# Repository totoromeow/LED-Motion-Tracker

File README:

Computer Science House - LED Motion Tracker 

Anqi Chen (c) 2012

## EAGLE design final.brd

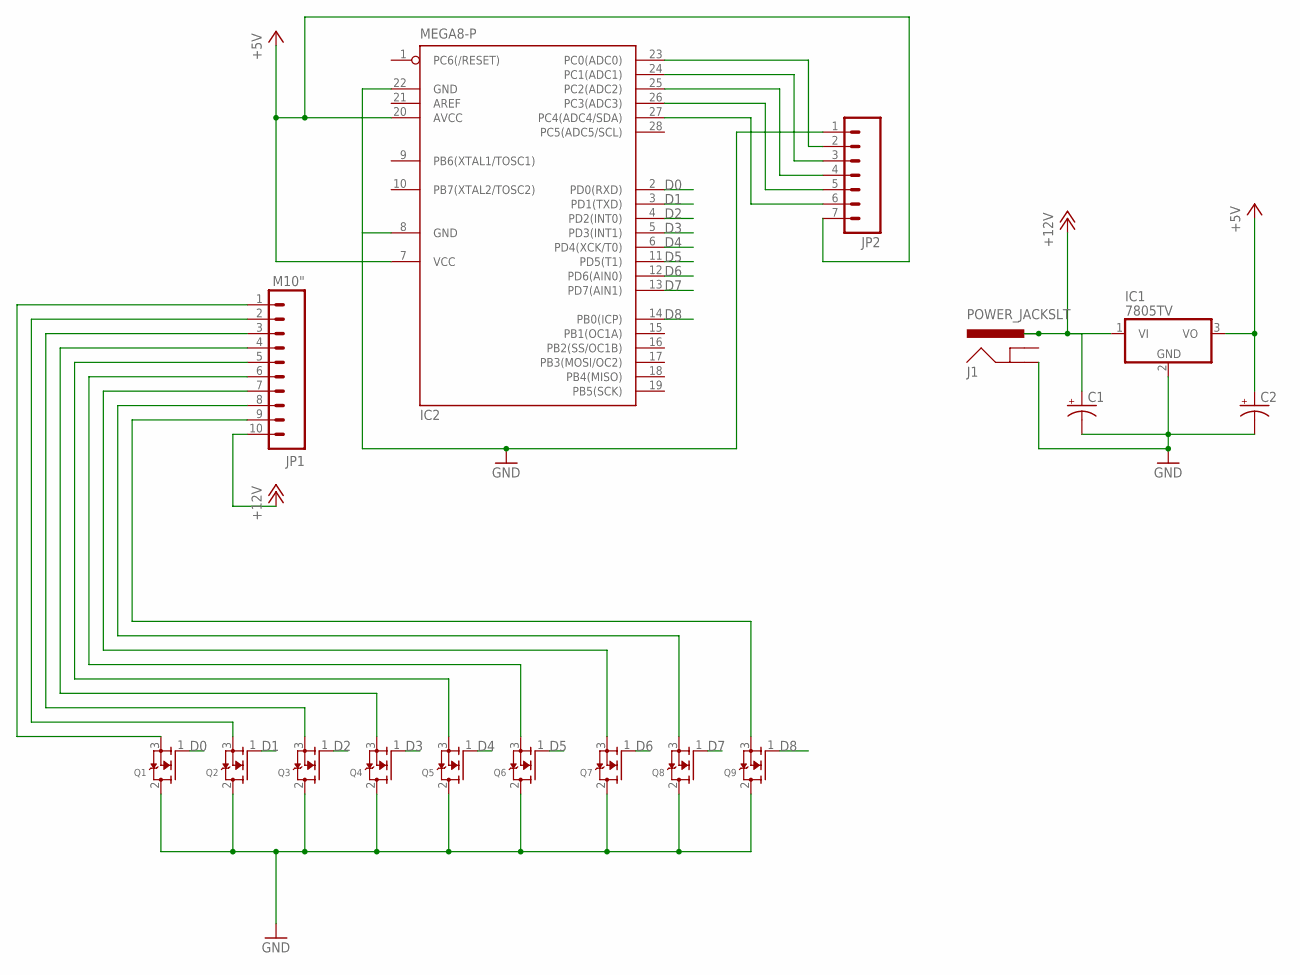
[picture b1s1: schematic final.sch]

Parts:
C1, C2: CAP_POLPTH1; CPOL-RADIAL-100UF-25V
IC1: 7805TV; TO220V
IC2: MEGA8-P; DIL28-3
J1: POWER_JACKSLT; POWER_JACK_SLOT
JP1: M10"; 1X10
JP2: M07; 1X07
Q1, Q2, Q3, Q4, Q5, Q6, Q7, Q8, Q9: MOSFET-NGDS_TO220V; TO220V

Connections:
+5V: C2.1 (+), IC1.3 (VO), IC2.7 (VCC), IC2.20 (AVCC), JP2.7
+12V: C1.1 (+), IC1.1 (VI), J1.PWR, JP1.10
D0: IC2.2 (PD0(RXD)), Q1.1 (G)
D1: IC2.3 (PD1(TXD)), Q2.1 (G)
D2: IC2.4 (PD2(INT0)), Q3.1 (G)
D3: IC2.5 (PD3(INT1)), Q4.1 (G)
D4: IC2.6 (PD4(XCK/T0)), Q5.1 (G)
D5: IC2.11 (PD5(T1)), Q6.1 (G)
D6: IC2.12 (PD6(AIN0)), Q7.1 (G)
D7: IC2.13 (PD7(AIN1)), Q8.1 (G)
D8: IC2.14 (PB0(ICP)), Q9.1 (G)
GND: C1.2 (-), C2.2 (-), IC1.2 (GND), IC2.8 (GND), IC2.22 (GND), J1.GND@2 (GND), JP2.1, Q1.2 (D), Q2.2 (D), Q3.2 (D), Q4.2 (D), Q5.2 (D), Q6.2 (D), Q7.2 (D), Q8.2 (D), Q9.2 (D)
unnamed: JP1.1, Q1.3 (S)
unnamed: JP1.2, Q2.3 (S)
unnamed: JP1.3, Q3.3 (S)
unnamed: IC2.27 (PC4(ADC4/SDA)), JP2.6
unnamed: IC2.23 (PC0(ADC0)), JP2.2
unnamed: IC2.24 (PC1(ADC1)), JP2.3
unnamed: IC2.25 (PC2(ADC2)), JP2.4
unnamed: IC2.26 (PC3(ADC3)), JP2.5
unnamed: JP1.4, Q4.3 (S)
unnamed: JP1.5, Q5.3 (S)
unnamed: JP1.6, Q6.3 (S)
unnamed: JP1.7, Q7.3 (S)
unnamed: JP1.8, Q8.3 (S)
unnamed: JP1.9, Q9.3 (S)

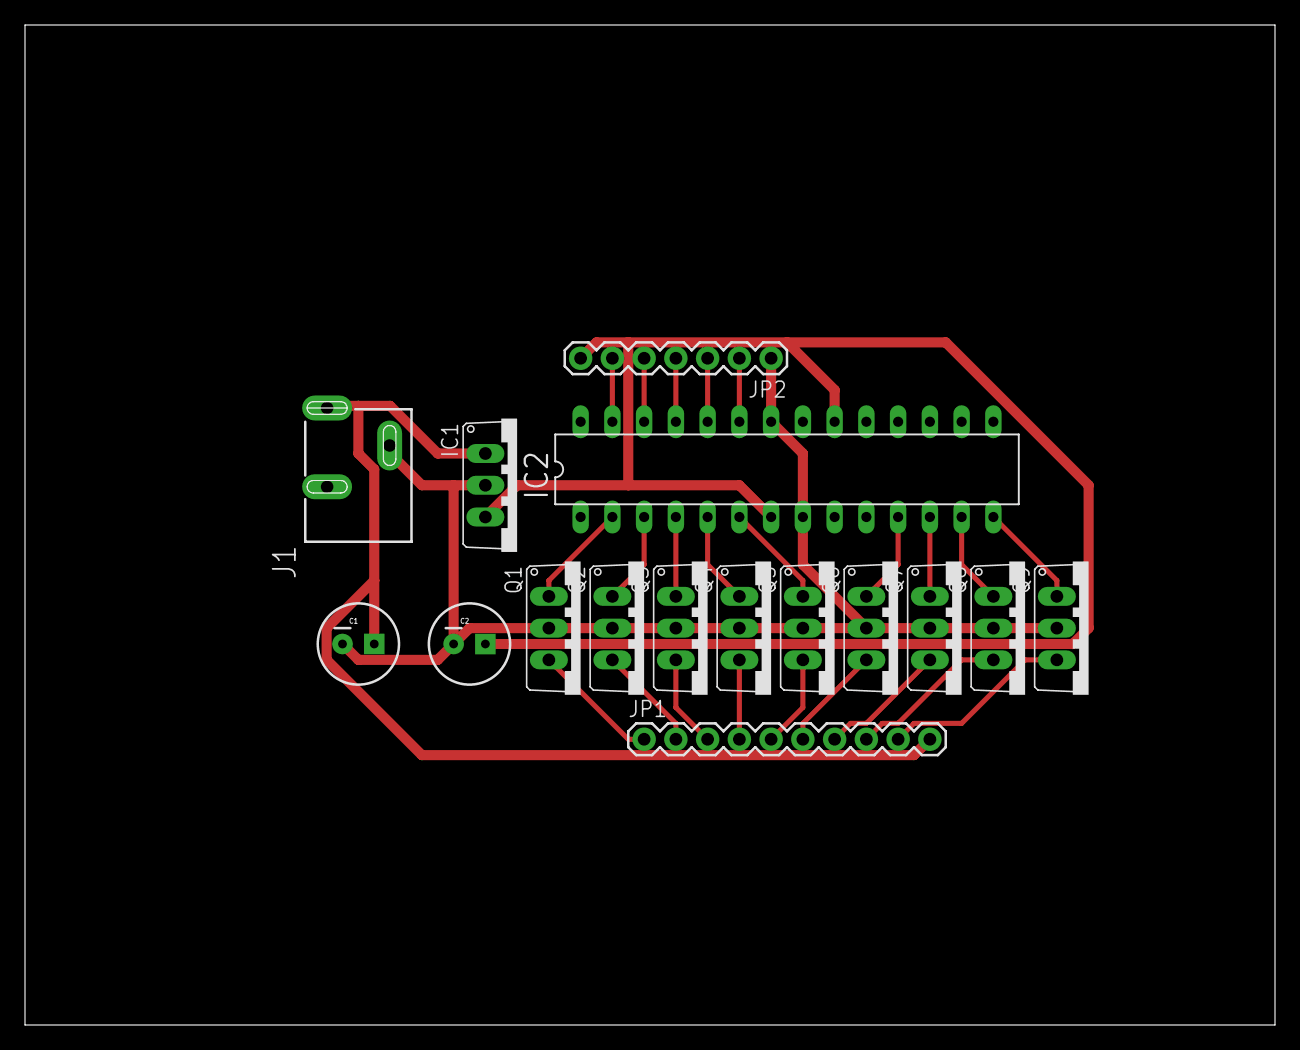
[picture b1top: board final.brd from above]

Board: 2 copper layers, 100.0 x 80.0 mm, 16 parts (0 on the bottom side), 26 nets.

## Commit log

2012-01-28 Initial Prototype finished
2012-03-17 ADC update
2012-03-17 full ADC function implemented
2012-03-17 PCB design file by Eagle Cadsoft
2012-03-17 final implementation
2012-03-17 device specific updates
2012-03-29 design update
2012-03-30 board update
2012-05-11 new ADC
2012-05-11 change
2016-02-10 squashed commits
    test 2
2016-02-10 squashed reverts

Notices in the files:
parts and their libraries:
SparkFun: Licensing: CC v3.0 Share-Alike You are welcome to use this library for commercial purposes.
